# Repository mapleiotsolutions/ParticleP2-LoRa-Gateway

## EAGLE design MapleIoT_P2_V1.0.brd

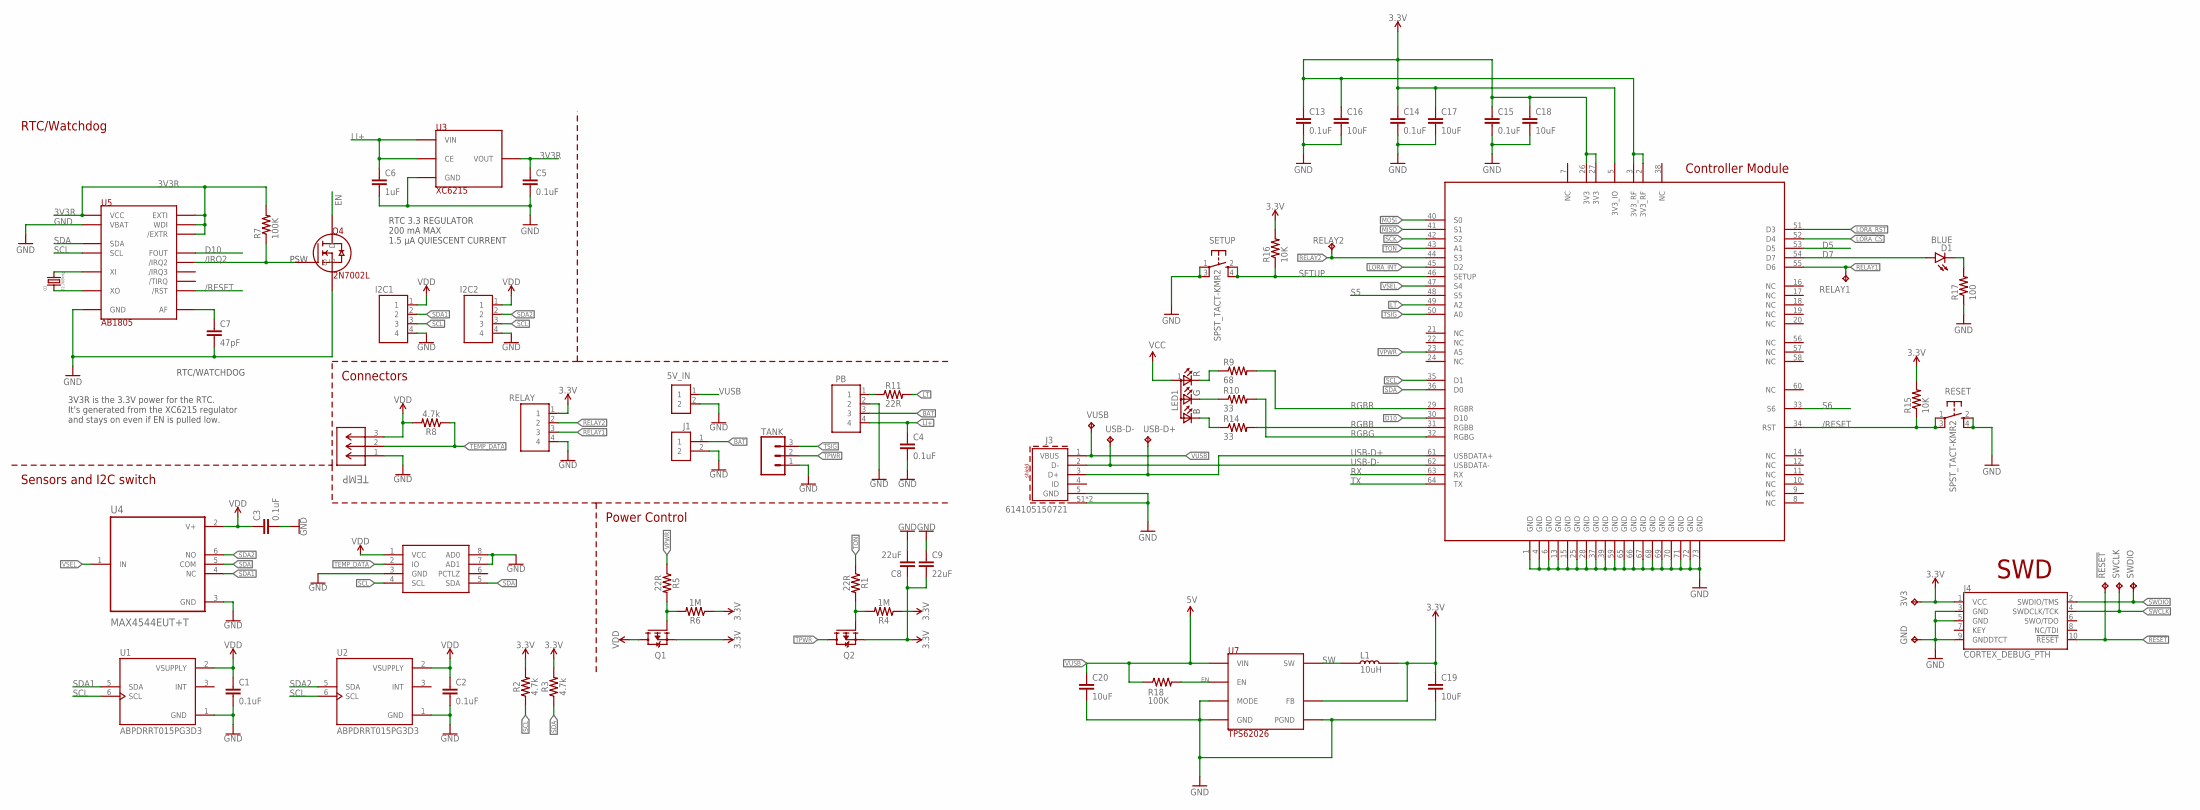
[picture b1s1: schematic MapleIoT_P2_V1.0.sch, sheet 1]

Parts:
3V3: TPTP15R; TP15R
5V_IN: B2B-XH-A(LF)(SN); SHDR2W64P0X250_1X2_740X575X700
!RESET: TPTP15R; TP15R
C1, C2, C3, C4: 0.1uF; C0603
C5, C13, C14, C15: 0.1uF; 0603-CAP
C6: 1uF; 0603-CAP
C7: 47pF; 0603-CAP
C8, C9: 22uF; C1206
C16, C17, C18, C19, C20: 10uF; 0603-CAP
D1: BLUE; LED-0603
GND: TPTP15R; TP15R
I2C1, I2C2: B4B-XH-A(LF)(SN); SHDR4W64P0X250_1X4_1240X575X70
J1: B2B-PH-K-S(LF)(SN); JST_B2B-PH-K-S(LF)(SN)
J3: 614105150721
J4: CORTEX_DEBUG_PTH; 2X5-PTH-1.27MM
L1: 10uH; BOURNS-INDUCTOR-3X3
LED1: LED-RGB-CREE-SMD
PB: B4B-XH-A(LF)(SN); SHDR4W64P0X250_1X4_1240X575X70
Q1, Q2: PMV65XP,215; SOT95P230X110-3N
Q3: 32.768kHz; ABS07-120-CRYSTAL
Q4: 2N7002L
R1, R5, R11: 22R; R0603
R2, R3, R8: 4.7k; R0603
R4, R6: 1M; R0603
R7: 100K; 0603-RES
R9: 68; 0603-RES
R10, R14: 33; 0603-RES
R15, R16: 10K; 0603-RES
R17: 100; 0603-RES
R18: 100K; R0603_P
RELAY: B4B-XH-A(LF)(SN); SHDR4W64P0X250_1X4_1240X575X70
RELAY1, RELAY2: TPTP15R; TP15R
RESET: SPST_TACT-KMR2; KMR2
SETUP: SPST_TACT-KMR2; KMR2
SWCLK: TPTP15R; TP15R
SWDIO: TPTP15R; TP15R
TANK: B3B-XH-A(LF)(SN); SHDR3W64P0X250_1X3
TEMP: B3B-PH-K-S(LF)(SN); CONN_B3B-PH-K-S(LF)(SN)_JST
U1, U2: ABPDRRT015PG3D3; XDCR_ABPDLNN100MG2A3
U3: XC6215; SOT-25-TOREX
U4: MAX4544EUT+T; SOT95P280X145-6N
U5: AB1805; 16-VFQFN-ABRACON
U7: TPS62026; 10-HVSSOP-TI
U$2: DS2482-100; 8-SOIC-MAXIM
U$3: P2
USB-D+: TPTP15R; TP15R
USB-D-: TPTP15R; TP15R
VUSB: TPTP15R; TP15R

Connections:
3.3V: 3V3.TP, C8.1, C9.2, C13.1, C14.1, C15.1, C16.1, C17.1, C18.1, C19.1, J4.1 (VCC), L1.2, Q1.2 (S), Q2.2 (S), R2.2, R3.2, R4.1, R6.1, R15.2, R16.2, RELAY.1, U7.5 (FB), U$3.2 (3V3_RF), U$3.3 (3V3_RF), U$3.5 (3V3_IO), U$3.26 (3V3), U$3.27 (3V3); also elsewhere on the board
3V3: LED1.1 (A)
3V3R: C5.1, R7.2, U3.5 (VOUT), U5.2 (WDI), U5.3 (/EXTR), U5.10 (EXTI), U5.13 (VCC)
!LORA_CS: U$3.52 (D4); also elsewhere on the board
!RESET: !RESET.TP, J4.10 (!RESET)
/IRQ2: Q4.1 (G), R7.1, U5.4 (/IRQ2)
/RESET: R15.1, RESET.1, RESET.3 (P1), U5.1 (/RST), U$3.34 (RST)
AF: C7.1, U5.14 (AF)
BAT: J1.1, PB.3
D5: U$3.53 (D5)
D7: D1.A, U$3.54 (D7)
D10: U5.11 (FOUT), U$3.30 (D10)
EN: Q4.3 (D), R18.2, U7.1 (EN)
GND: 5V_IN.2, C1.2, C2.2, C3.2, C4.2, C5.2, C6.2, C7.2, C8.2, C9.1, C13.2, C14.2, C15.2, C16.2, C17.2, C18.2, C19.2, C20.2, GND.TP, I2C1.4, I2C2.4, J1.2, J3.5 (GND), J3.S1 (SHIELD), J3.S2 (SHIELD), J4.3 (GND), J4.5 (GND), J4.9 (GNDDTCT), PB.2, Q4.2 (S), R17.1, RELAY.4, RESET.2 (S), RESET.4 (S1), SETUP.1, SETUP.3 (P1), TANK.1, TEMP.1, U1.1 (GND), U2.1 (GND), U3.2 (GND), U4.3 (GND), U5.5 (VBAT), U5.9 (GND), U5.EP (GND), U7.4 (GND), U7.6 (MODE), U7.9 (PGND), U7.10 (PGND), U7.P (GND), U$2.3 (GND), U$2.7 (AD1), U$2.8 (AD0), U$3.1 (GND), U$3.4 (GND), U$3.6 (GND), U$3.13 (GND), U$3.15 (GND), U$3.25 (GND), U$3.28 (GND), U$3.37 (GND), U$3.39 (GND), U$3.59 (GND), U$3.65 (GND), U$3.66 (GND), U$3.67 (GND), U$3.68 (GND), U$3.69 (GND), U$3.70 (GND), U$3.71 (GND), U$3.72 (GND), U$3.73 (GND); also elsewhere on the board
LI+: C4.1, C6.1, PB.4, U3.1 (VIN), U3.3 (CE)
LORA_INT: U$3.45 (D2); also elsewhere on the board
LORA_RST: U$3.51 (D3); also elsewhere on the board
LT: R11.2, U$3.49 (A2)
MISO: U$3.41 (S1); also elsewhere on the board
MOSI: U$3.40 (S0); also elsewhere on the board
unnamed: Q2.1 (G), R1.2, R4.2
unnamed: Q1.1 (G), R5.2, R6.2
unnamed: PB.1, R11.1
unnamed: D1.C, R17.2
unnamed: LED1.4 (R), R9.1
unnamed: LED1.3 (G), R10.1
unnamed: LED1.2 (B), R14.1
RELAY1: RELAY.3, RELAY1.TP, U$3.55 (D6)
RELAY2: RELAY.2, RELAY2.TP, U$3.44 (S3)
RGBB: R14.2, U$3.31 (RGBB)
RGBG: R10.2, U$3.32 (RGBG)
RGBR: R9.2, U$3.29 (RGBR)
RX: U$3.63 (RX)
S5: U$3.48 (S5)
S6: U$3.33 (S6)
SCK: U$3.42 (S2); also elsewhere on the board
SCL: I2C1.3, I2C2.3, R2.1, U1.6 (SCL), U2.6 (SCL), U5.7 (SCL), U$2.4 (SCL), U$3.35 (D1)
SDA: R3.1, U4.5 (COM), U5.6 (SDA), U$2.5 (SDA), U$3.36 (D0)
SDA1: I2C1.2, U1.5 (SDA), U4.4 (NC)
SDA2: I2C2.2, U2.5 (SDA), U4.6 (NO)
SETUP: R16.1, SETUP.2 (S), SETUP.4 (S1), U$3.46 (SETUP)
SW: L1.1, U7.7 (SW), U7.8 (SW)
SWCLK: J4.4 (SWDCLK/TCK), SWCLK.TP
SWDIO: J4.2 (SWDIO/TMS), SWDIO.TP
TEMP_DATA: R8.1, TEMP.2, U$2.2 (IO)
TON: R1.1, U$3.43 (A1)
TPWR: Q2.3 (D), TANK.2
TSIG: TANK.3, U$3.50 (A0)
TX: U$3.64 (TX)
USB-D+: J3.3 (D+), U$3.61 (USBDATA+), USB-D+.TP
USB-D-: J3.2 (D-), U$3.62 (USBDATA-), USB-D-.TP
VDD: C1.1, C2.1, C3.1, I2C1.1, I2C2.1, Q1.3 (D), R8.2, TEMP.3, U1.2 (VSUPPLY), U2.2 (VSUPPLY), U4.2 (V+), U$2.1 (VCC)
VPWR: R5.1, U$3.23 (A5)
VSEL: U4.1 (IN), U$3.47 (S4)
VUSB: 5V_IN.1, C20.1, J3.1 (VBUS), R18.1, U7.2 (VIN), U7.3 (VIN), VUSB.TP
XI: Q3.2, U5.16 (XI)
XO: Q3.1, U5.15 (XO)

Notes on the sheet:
RTC/Watchdog
Connectors
Sensors and I2C switch
Power Control
RTC 3.3 REGULATOR 200 mA MAX 1.5 µA QUIESCENT CURRENT
PSW
RTC/WATCHDOG
3V3R is the 3.3V power for the RTC. It's generated from the XC6215 regulator and stays on even if EN is pulled low.
Controller Module
SWD

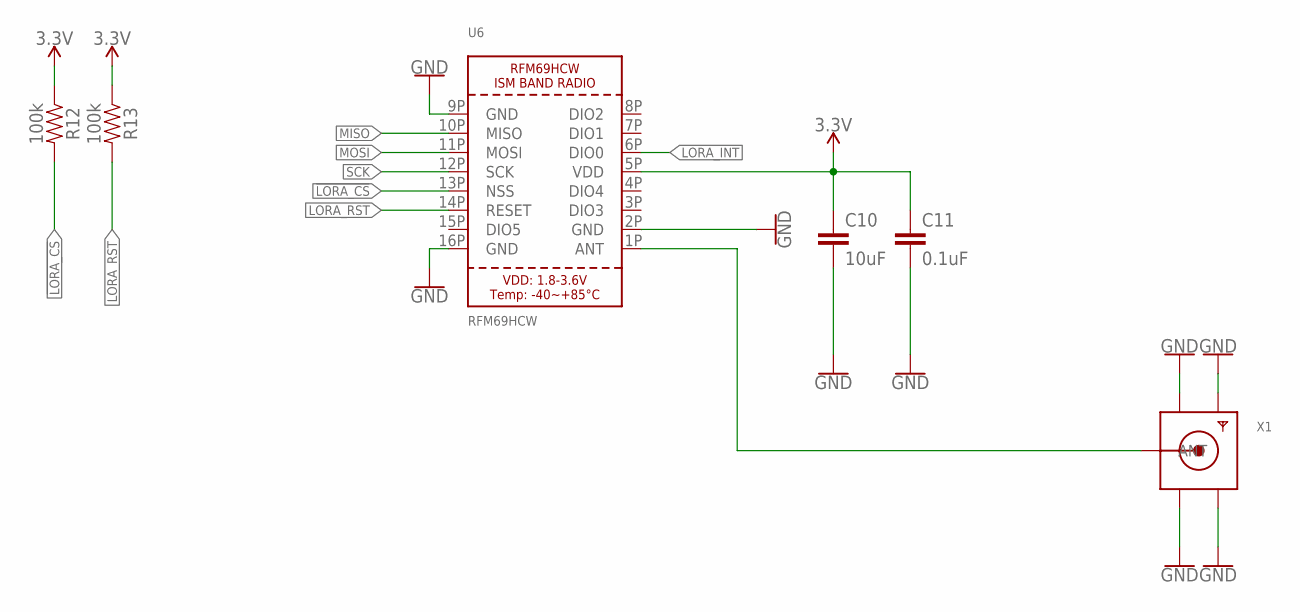
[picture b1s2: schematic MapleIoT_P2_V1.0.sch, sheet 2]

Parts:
C10: 10uF; C0603
C11: 0.1uF; C0603
R12, R13: 100k; R0603
U6: RFM69HCW; RFMHCW_SMT
X1: SMACONNECTOR; SMA90_DIP

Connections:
3.3V: C10.1, C11.1, R12.1, R13.1, U6.5P (VDD); also elsewhere on the board
!LORA_CS: R12.2, U6.13P (NSS); also elsewhere on the board
GND: C10.2, C11.2, U6.2P (GND), U6.9P (GND), U6.16P (GND), X1.GND1, X1.GND2, X1.GND3, X1.GND4; also elsewhere on the board
LORA_INT: U6.6P (DIO0); also elsewhere on the board
LORA_RST: R13.2, U6.14P (RESET); also elsewhere on the board
MISO: U6.10P (MISO); also elsewhere on the board
MOSI: U6.11P (MOSI); also elsewhere on the board
unnamed: U6.1P (ANT), X1.ANTENNA (ANT)
SCK: U6.12P (SCK); also elsewhere on the board

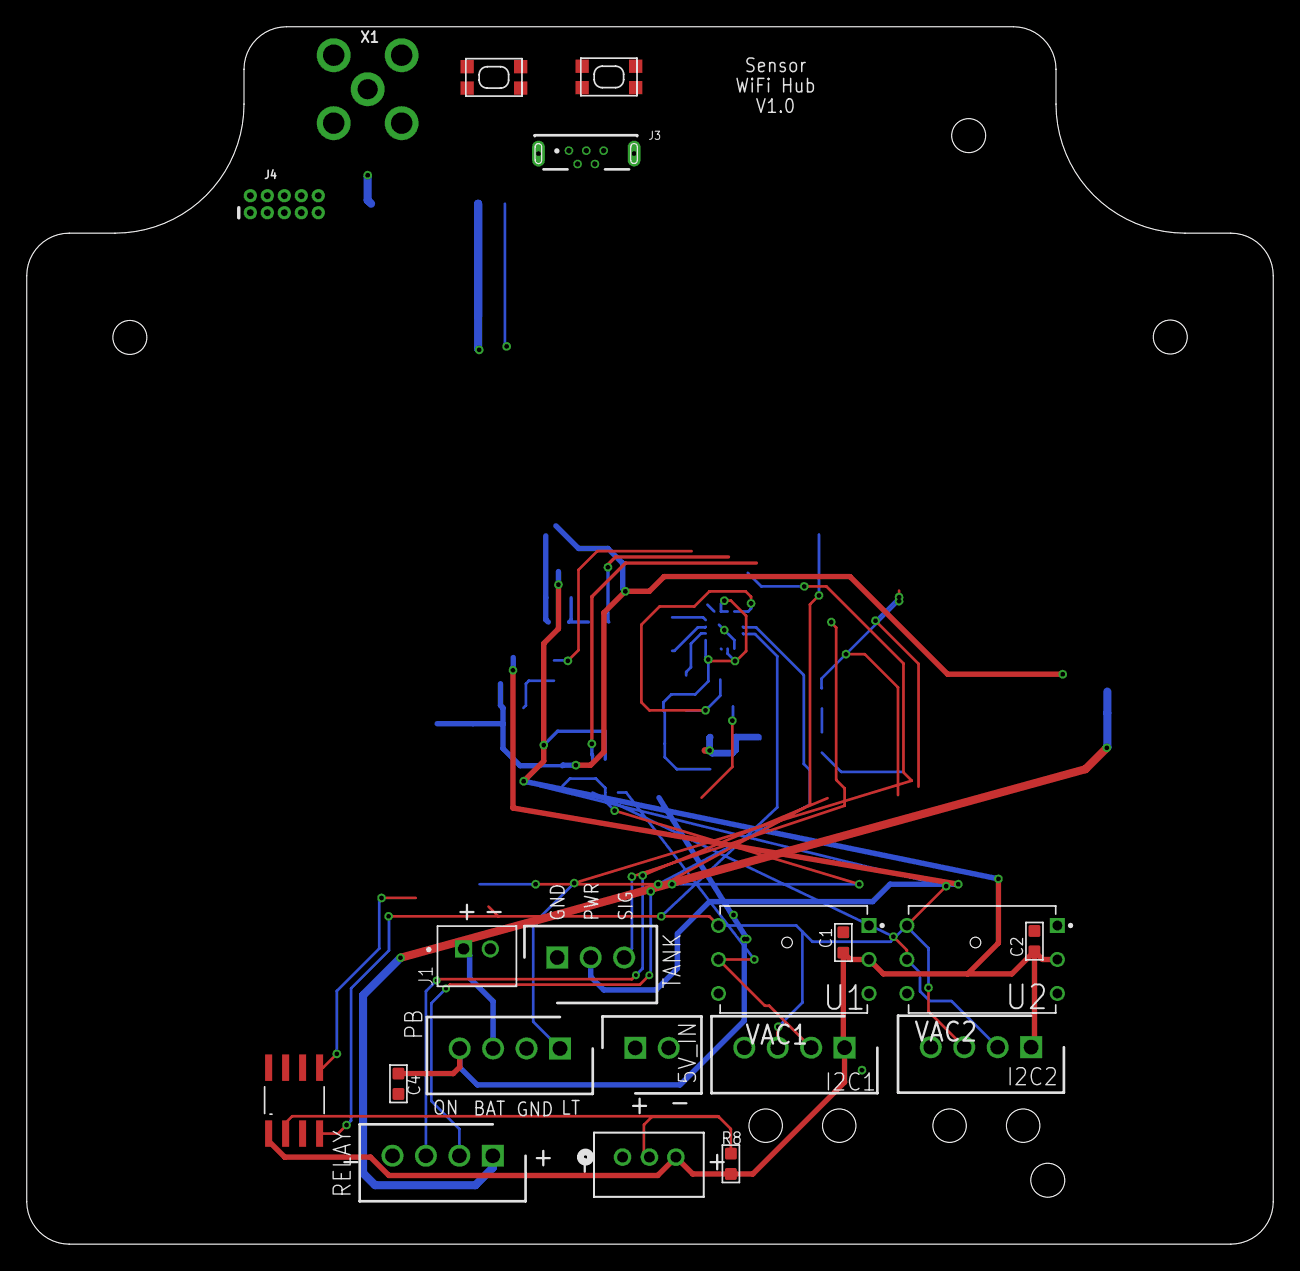
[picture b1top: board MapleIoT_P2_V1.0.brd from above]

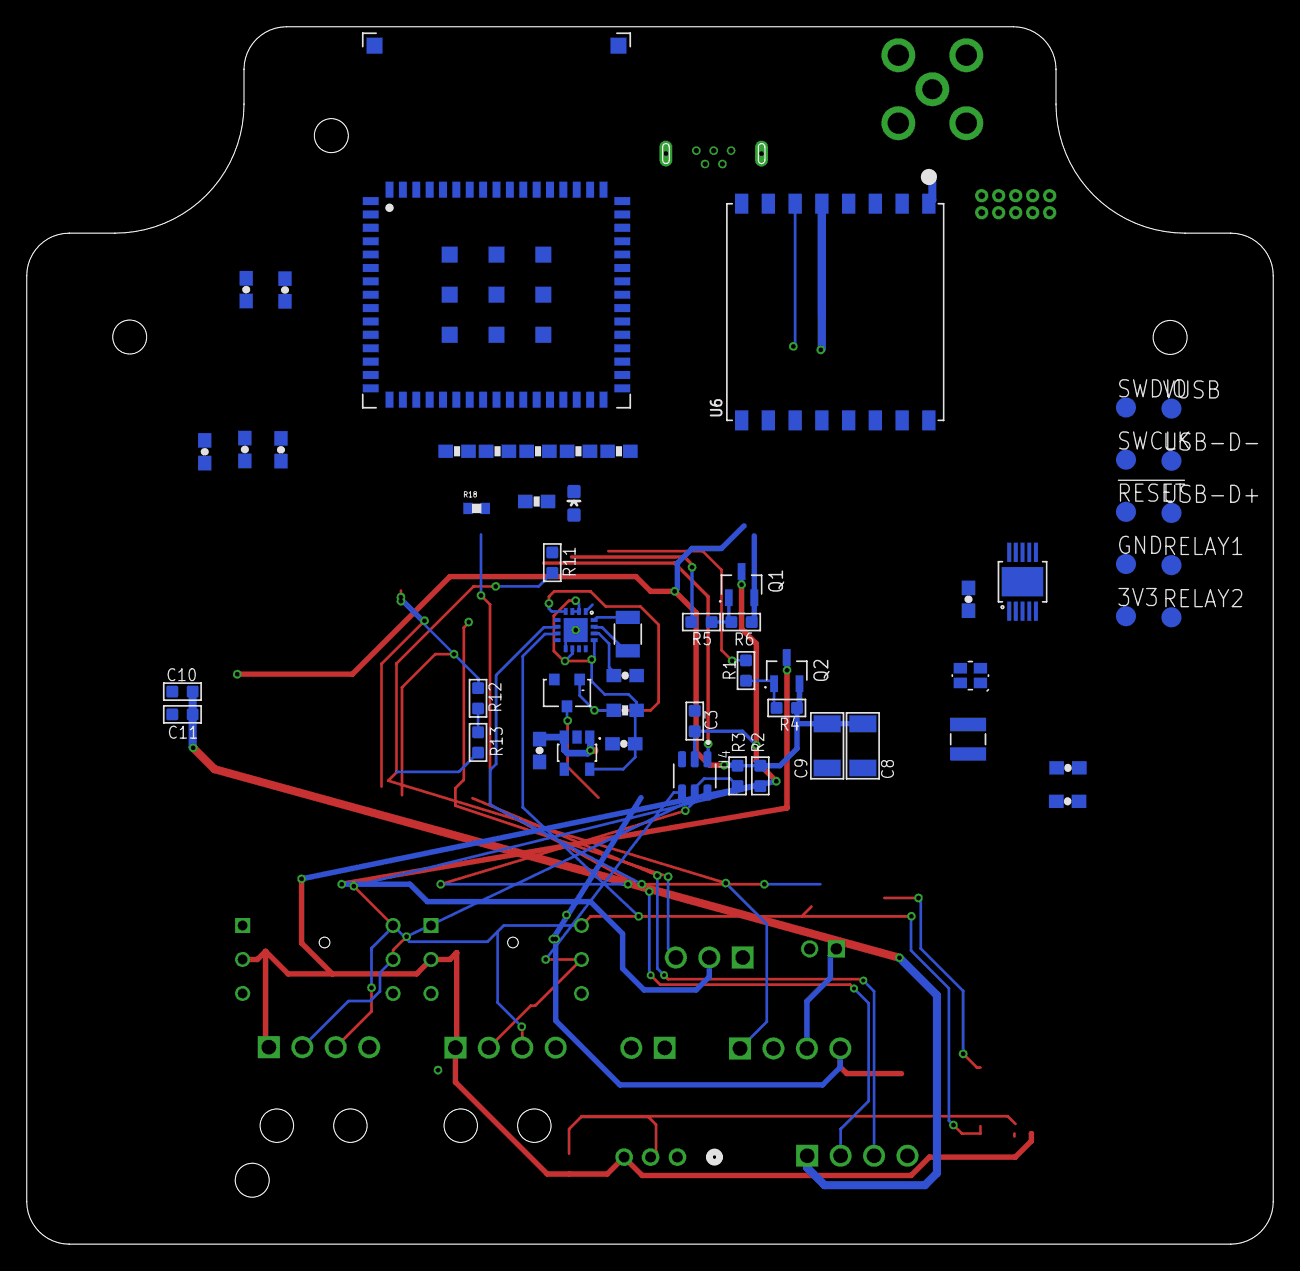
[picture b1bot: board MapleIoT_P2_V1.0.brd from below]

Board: 2 copper layers, 93.2 x 91.0 mm, 76 parts (56 on the bottom side), 52 nets.

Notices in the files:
parts and their libraries:
microbuilder: This work is placed in the public domain, and may be freely used for commercial and non-commercial work with the following conditions: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
SparkFun-Connectors: Licensing: Creative Commons ShareAlike 4.0 International - https://creativecommons.org/licenses/by-sa/4.0
